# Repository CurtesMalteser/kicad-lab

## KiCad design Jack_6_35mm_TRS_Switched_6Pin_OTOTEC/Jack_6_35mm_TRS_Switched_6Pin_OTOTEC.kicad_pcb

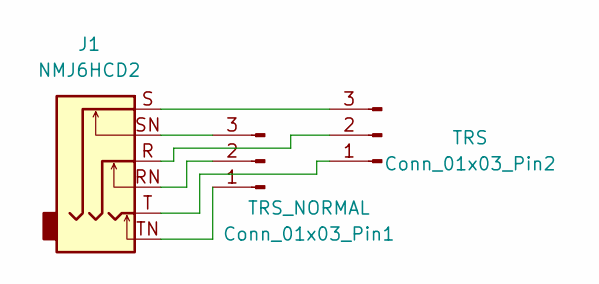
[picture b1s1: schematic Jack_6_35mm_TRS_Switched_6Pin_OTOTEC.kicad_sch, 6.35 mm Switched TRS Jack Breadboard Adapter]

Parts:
Conn_01x03_Pin1: TRS_NORMAL; PinHeader_1x03_P2.54mm_Vertical
Conn_01x03_Pin2: TRS; PinHeader_1x03_P2.54mm_Vertical
J1: NMJ6HCD2; Jack_6.35mm_OTOTEC_TRS_Switched_6Pin

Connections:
unnamed: Conn_01x03_Pin1.1, J1.TN
unnamed: Conn_01x03_Pin1.2, J1.RN
unnamed: Conn_01x03_Pin1.3, J1.SN
unnamed: Conn_01x03_Pin2.1, J1.T
unnamed: Conn_01x03_Pin2.2, J1.R
unnamed: Conn_01x03_Pin2.3, J1.S

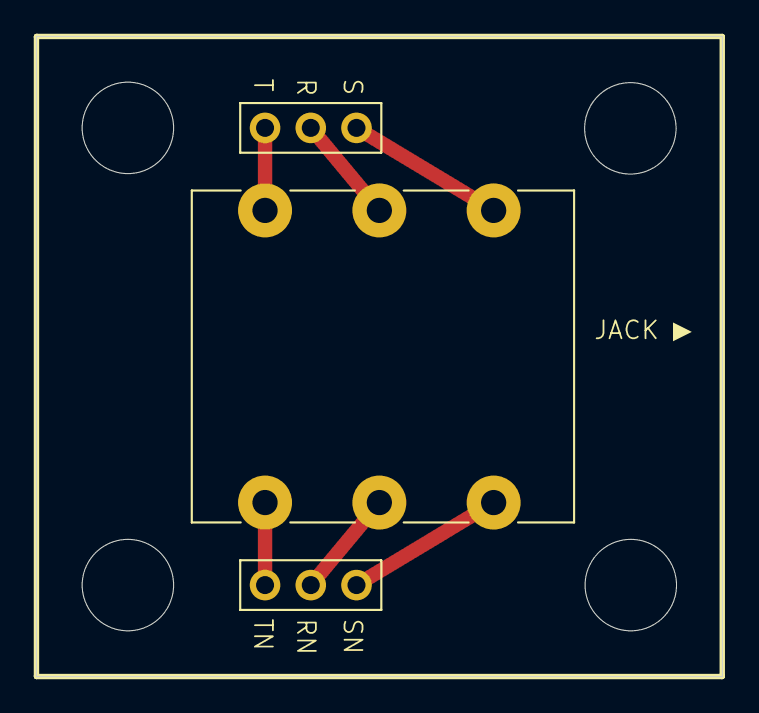
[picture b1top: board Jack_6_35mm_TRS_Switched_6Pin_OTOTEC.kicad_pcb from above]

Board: 2 copper layers, 38.1 x 35.6 mm, 3 parts (0 on the bottom side), 6 nets.
